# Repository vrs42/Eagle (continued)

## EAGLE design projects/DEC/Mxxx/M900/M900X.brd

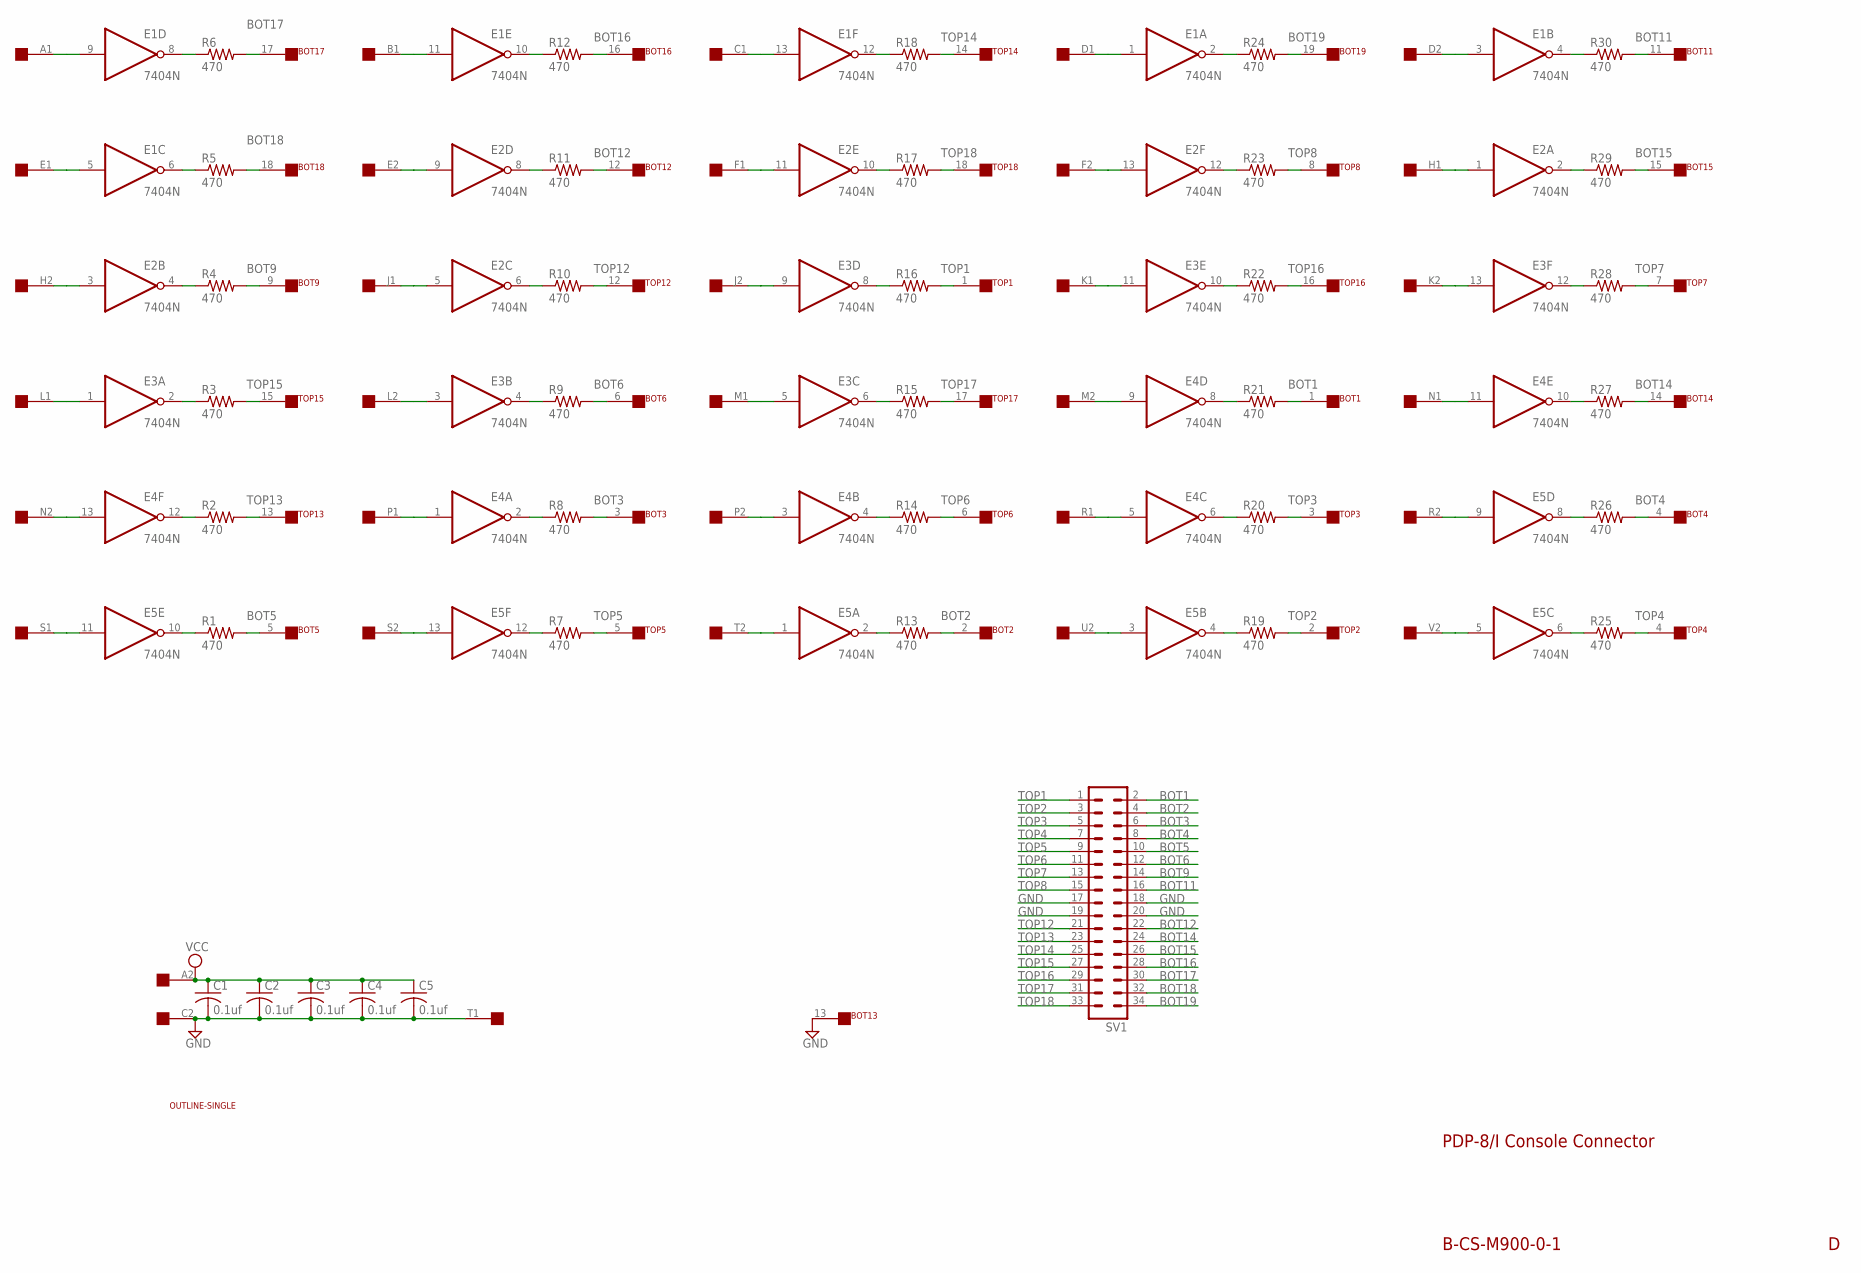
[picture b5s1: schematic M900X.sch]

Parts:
BOT: FLEX19
C1, C2, C3, C4, C5: 0.1uf; C050-025X075
E1, E2, E3, E4, E5: 7404N; DIL14
EDGE: SINGLE; EDGE-CON2
R1, R2, R3, R4, R5, R6, R7, R8, R9, R10, R11, R12, R13, R14, R15, R16, R17, R18, R19, R20, R21, R22, R23, R24, R25, R26, R27, R28, R29, R30: 470; 0207/10
SV1: ML34L
TOP: FLEX19
U$2: OUTLINE-SINGLE; SINGLE

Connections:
BOT1: BOT.1, R21.2, SV1.2
BOT2: BOT.2, R13.2, SV1.4
BOT3: BOT.3, R8.2, SV1.6
BOT4: BOT.4, R26.2, SV1.8
BOT5: BOT.5, R1.2, SV1.10
BOT6: BOT.6, R9.2, SV1.12
BOT9: BOT.9, R4.2, SV1.14
BOT11: BOT.11, R30.2, SV1.16
BOT12: BOT.12, R11.2, SV1.22
BOT14: BOT.14, R27.2, SV1.24
BOT15: BOT.15, R29.2, SV1.26
BOT16: BOT.16, R12.2, SV1.28
BOT17: BOT.17, R6.2, SV1.30
BOT18: BOT.18, R5.2, SV1.32
BOT19: BOT.19, R24.2, SV1.34
GND: BOT.13, C1.2, C2.2, C3.2, C4.2, C5.2, E1.7 (GND), E2.7 (GND), E3.7 (GND), E4.7 (GND), E5.7 (GND), EDGE.C2, EDGE.T1, SV1.17, SV1.18, SV1.19, SV1.20
unnamed: E1.9 (I), EDGE.A1
unnamed: E1.8 (O), R6.1
unnamed: E1.6 (O), R5.1
unnamed: E2.4 (O), R4.1
unnamed: E3.2 (O), R3.1
unnamed: E4.12 (O), R2.1
unnamed: E2.3 (I), EDGE.H2
unnamed: E5.11 (I), EDGE.S1
unnamed: E4.13 (I), EDGE.N2
unnamed: E3.1 (I), EDGE.L1
unnamed: E1.5 (I), EDGE.E1
unnamed: E4.1 (I), EDGE.P1
unnamed: E1.11 (I), EDGE.B1
unnamed: E2.9 (I), EDGE.E2
unnamed: E2.5 (I), EDGE.J1
unnamed: E3.3 (I), EDGE.L2
unnamed: E5.13 (I), EDGE.S2
unnamed: E4.2 (O), R8.1
unnamed: E3.4 (O), R9.1
unnamed: E2.6 (O), R10.1
unnamed: E2.8 (O), R11.1
unnamed: E1.10 (O), R12.1
unnamed: E5.12 (O), R7.1
unnamed: E5.10 (O), R1.1
unnamed: E4.3 (I), EDGE.P2
unnamed: E1.13 (I), EDGE.C1
unnamed: E2.11 (I), EDGE.F1
unnamed: E3.9 (I), EDGE.J2
unnamed: E3.5 (I), EDGE.M1
unnamed: E5.1 (I), EDGE.T2
unnamed: E5.2 (O), R13.1
unnamed: E4.4 (O), R14.1
unnamed: E3.6 (O), R15.1
unnamed: E3.8 (O), R16.1
unnamed: E1.12 (O), R18.1
unnamed: E2.10 (O), R17.1
unnamed: E5.4 (O), R19.1
unnamed: E4.6 (O), R20.1
unnamed: E4.8 (O), R21.1
unnamed: E3.10 (O), R22.1
unnamed: E2.12 (O), R23.1
unnamed: E1.2 (O), R24.1
unnamed: E4.5 (I), EDGE.R1
unnamed: E2.13 (I), EDGE.F2
unnamed: E3.11 (I), EDGE.K1
unnamed: E4.9 (I), EDGE.M2
unnamed: E5.3 (I), EDGE.U2
unnamed: E5.9 (I), EDGE.R2
unnamed: E1.1 (I), EDGE.D1
unnamed: E1.3 (I), EDGE.D2
unnamed: E2.1 (I), EDGE.H1
unnamed: E3.13 (I), EDGE.K2
unnamed: E4.11 (I), EDGE.N1
unnamed: E5.5 (I), EDGE.V2
unnamed: E5.6 (O), R25.1
unnamed: E5.8 (O), R26.1
unnamed: E4.10 (O), R27.1
unnamed: E3.12 (O), R28.1
unnamed: E2.2 (O), R29.1
unnamed: E1.4 (O), R30.1
TOP1: R16.2, SV1.1, TOP.1
TOP2: R19.2, SV1.3, TOP.2
TOP3: R20.2, SV1.5, TOP.3
TOP4: R25.2, SV1.7, TOP.4
TOP5: R7.2, SV1.9, TOP.5
TOP6: R14.2, SV1.11, TOP.6
TOP7: R28.2, SV1.13, TOP.7
TOP8: R23.2, SV1.15, TOP.8
TOP12: R10.2, SV1.21, TOP.12
TOP13: R2.2, SV1.23, TOP.13
TOP14: R18.2, SV1.25, TOP.14
TOP15: R3.2, SV1.27, TOP.15
TOP16: R22.2, SV1.29, TOP.16
TOP17: R15.2, SV1.31, TOP.17
TOP18: R17.2, SV1.33, TOP.18
VCC: C1.1, C2.1, C3.1, C4.1, C5.1, E1.14 (VCC), E2.14 (VCC), E3.14 (VCC), E4.14 (VCC), E5.14 (VCC), EDGE.A2

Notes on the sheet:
B-CS-M900-0-1
PDP-8/I Console Connector

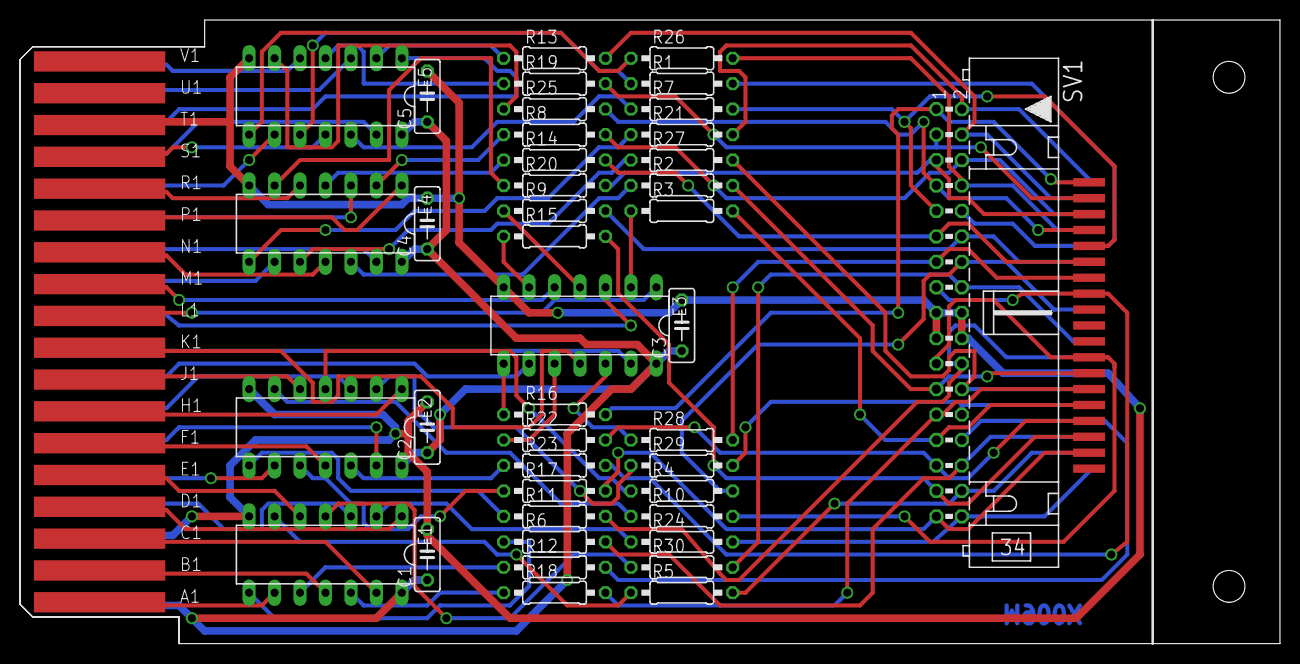
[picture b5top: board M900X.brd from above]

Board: 2 copper layers, 125.7 x 62.2 mm, 45 parts (1 on the bottom side), 92 nets.

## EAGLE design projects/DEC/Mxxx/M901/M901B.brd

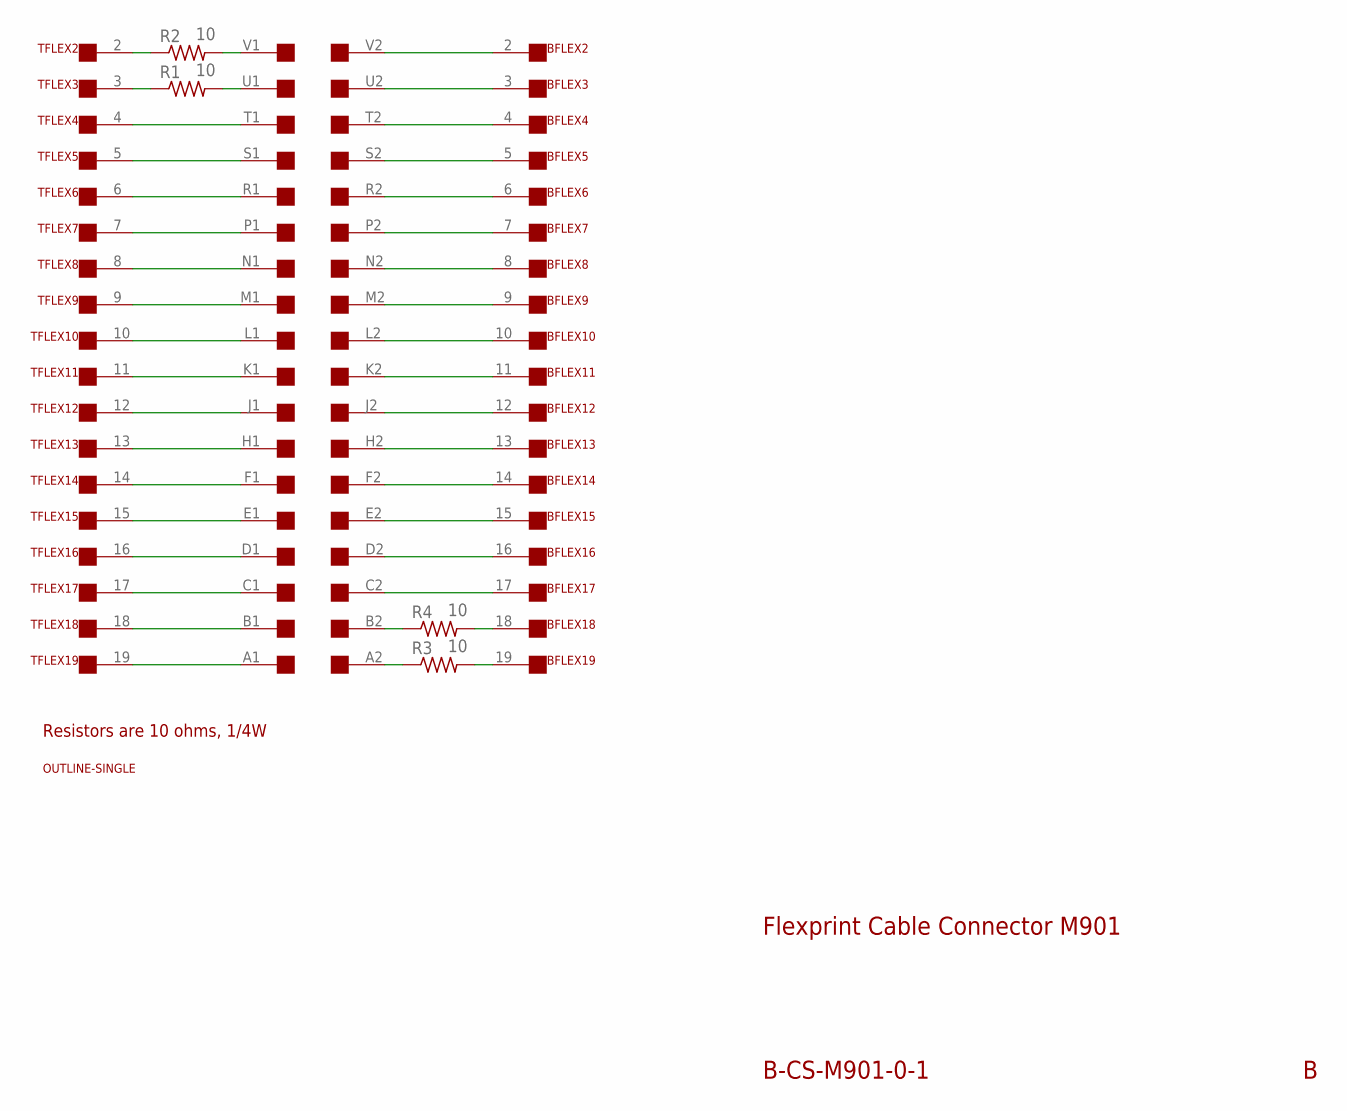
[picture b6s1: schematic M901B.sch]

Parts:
BFLEX: FLEX19
R1, R2, R3, R4: 10; 0207/10
TFLEX: FLEX19
U$1: SINGLE; EDGE-CON2
U$2: OUTLINE-SINGLE; SINGLE

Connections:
unnamed: TFLEX.4, U$1.T1
unnamed: TFLEX.19, U$1.A1
unnamed: TFLEX.17, U$1.C1
unnamed: TFLEX.16, U$1.D1
unnamed: TFLEX.15, U$1.E1
unnamed: TFLEX.14, U$1.F1
unnamed: TFLEX.13, U$1.H1
unnamed: TFLEX.12, U$1.J1
unnamed: TFLEX.11, U$1.K1
unnamed: TFLEX.10, U$1.L1
unnamed: TFLEX.9, U$1.M1
unnamed: TFLEX.8, U$1.N1
unnamed: TFLEX.7, U$1.P1
unnamed: TFLEX.6, U$1.R1
unnamed: TFLEX.5, U$1.S1
unnamed: BFLEX.3, U$1.U2
unnamed: BFLEX.6, U$1.R2
unnamed: BFLEX.8, U$1.N2
unnamed: BFLEX.10, U$1.L2
unnamed: BFLEX.12, U$1.J2
unnamed: BFLEX.14, U$1.F2
unnamed: BFLEX.16, U$1.D2
unnamed: BFLEX.15, U$1.E2
unnamed: BFLEX.17, U$1.C2
unnamed: BFLEX.13, U$1.H2
unnamed: R3.1, U$1.A2
unnamed: BFLEX.11, U$1.K2
unnamed: BFLEX.19, R3.2
unnamed: BFLEX.9, U$1.M2
unnamed: BFLEX.18, R4.2
unnamed: BFLEX.7, U$1.P2
unnamed: R4.1, U$1.B2
unnamed: BFLEX.5, U$1.S2
unnamed: BFLEX.4, U$1.T2
unnamed: R2.1, TFLEX.2
unnamed: BFLEX.2, U$1.V2
unnamed: R1.1, TFLEX.3
unnamed: R1.2, U$1.U1
unnamed: R2.2, U$1.V1
unnamed: TFLEX.18, U$1.B1

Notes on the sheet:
Flexprint Cable Connector M901
B-CS-M901-0-1
Resistors are 10 ohms, 1/4W

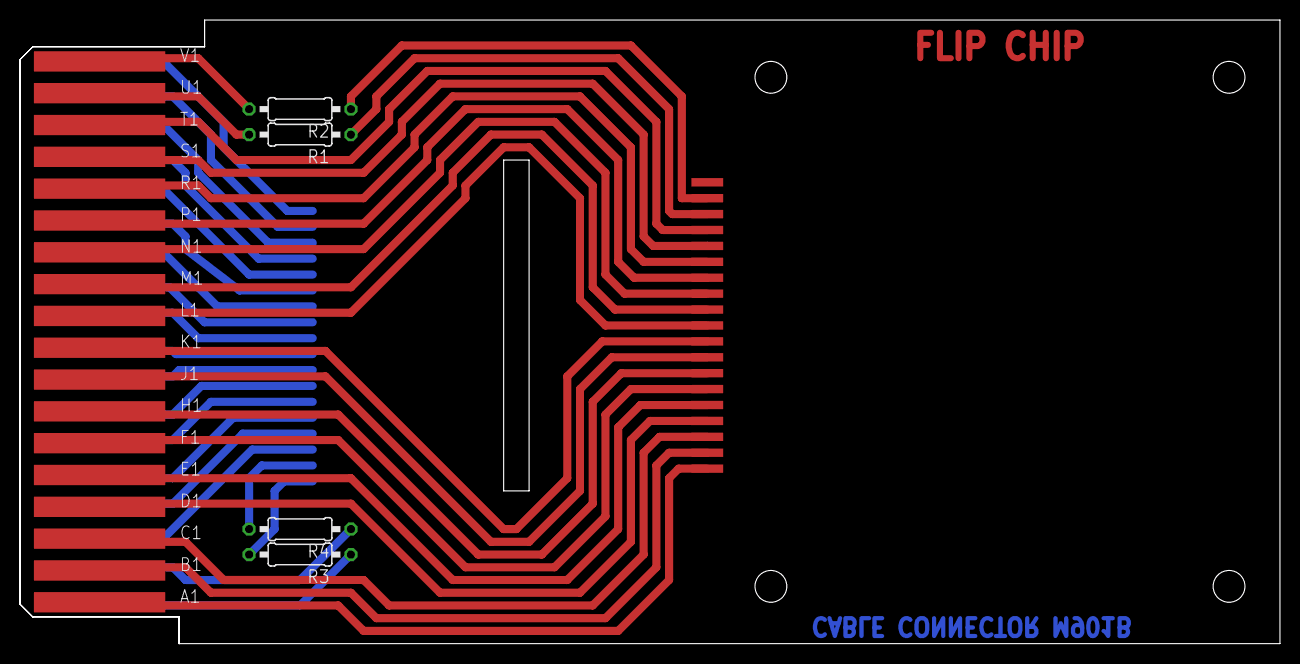
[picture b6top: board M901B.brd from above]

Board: 2 copper layers, 125.7 x 62.2 mm, 9 parts (1 on the bottom side), 40 nets.

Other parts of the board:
U$3: FLIPCHIP

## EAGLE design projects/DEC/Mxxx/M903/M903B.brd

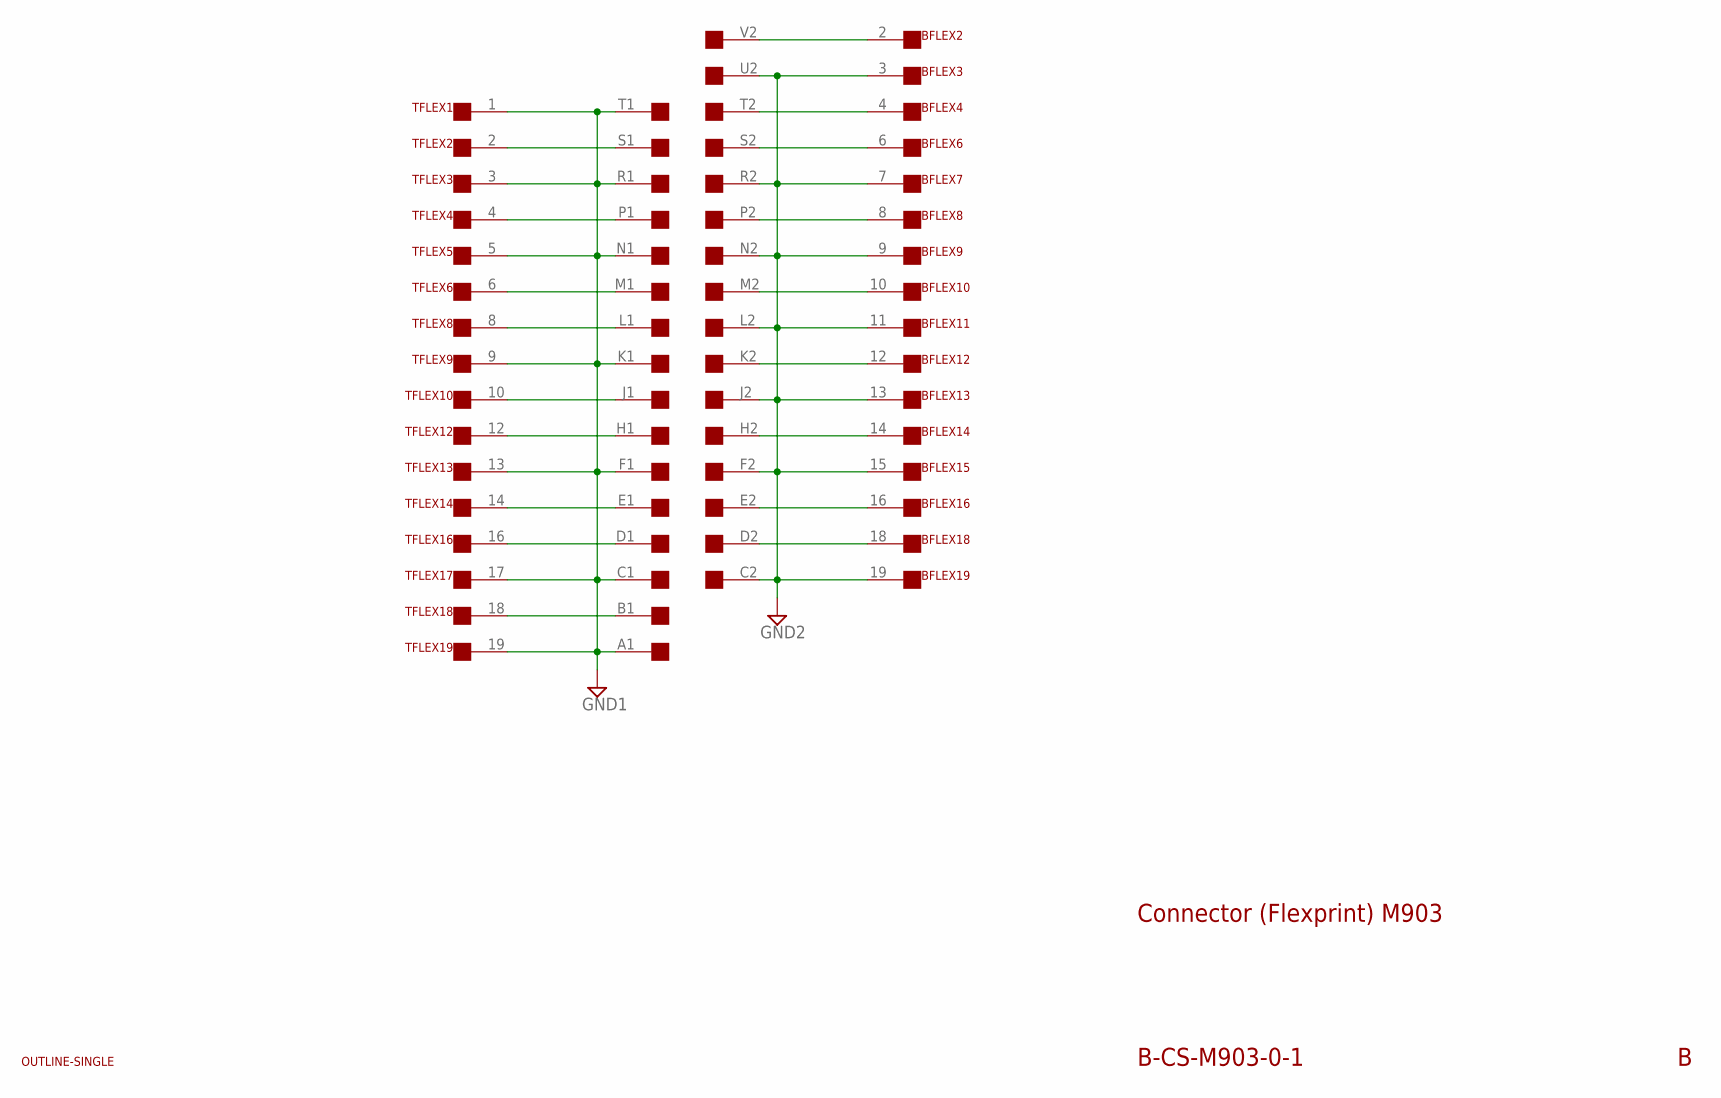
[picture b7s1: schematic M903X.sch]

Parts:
BFLEX: FLEX19
TFLEX: FLEX19
U$1: SINGLE; EDGE-CON2
U$2: OUTLINE-SINGLE; SINGLE

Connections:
GND1: TFLEX.1, TFLEX.3, TFLEX.5, TFLEX.9, TFLEX.13, TFLEX.17, TFLEX.19, U$1.A1, U$1.C1, U$1.F1, U$1.K1, U$1.N1, U$1.R1, U$1.T1
GND2: BFLEX.3, BFLEX.7, BFLEX.9, BFLEX.11, BFLEX.13, BFLEX.15, BFLEX.19, U$1.C2, U$1.F2, U$1.J2, U$1.L2, U$1.N2, U$1.R2, U$1.U2
unnamed: TFLEX.16, U$1.D1
unnamed: TFLEX.14, U$1.E1
unnamed: TFLEX.12, U$1.H1
unnamed: TFLEX.10, U$1.J1
unnamed: TFLEX.8, U$1.L1
unnamed: TFLEX.6, U$1.M1
unnamed: TFLEX.4, U$1.P1
unnamed: TFLEX.2, U$1.S1
unnamed: BFLEX.18, U$1.D2
unnamed: BFLEX.16, U$1.E2
unnamed: BFLEX.14, U$1.H2
unnamed: BFLEX.12, U$1.K2
unnamed: BFLEX.10, U$1.M2
unnamed: BFLEX.8, U$1.P2
unnamed: BFLEX.6, U$1.S2
unnamed: BFLEX.4, U$1.T2
unnamed: BFLEX.2, U$1.V2
unnamed: TFLEX.18, U$1.B1

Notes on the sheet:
Connector (Flexprint) M903
B-CS-M903-0-1

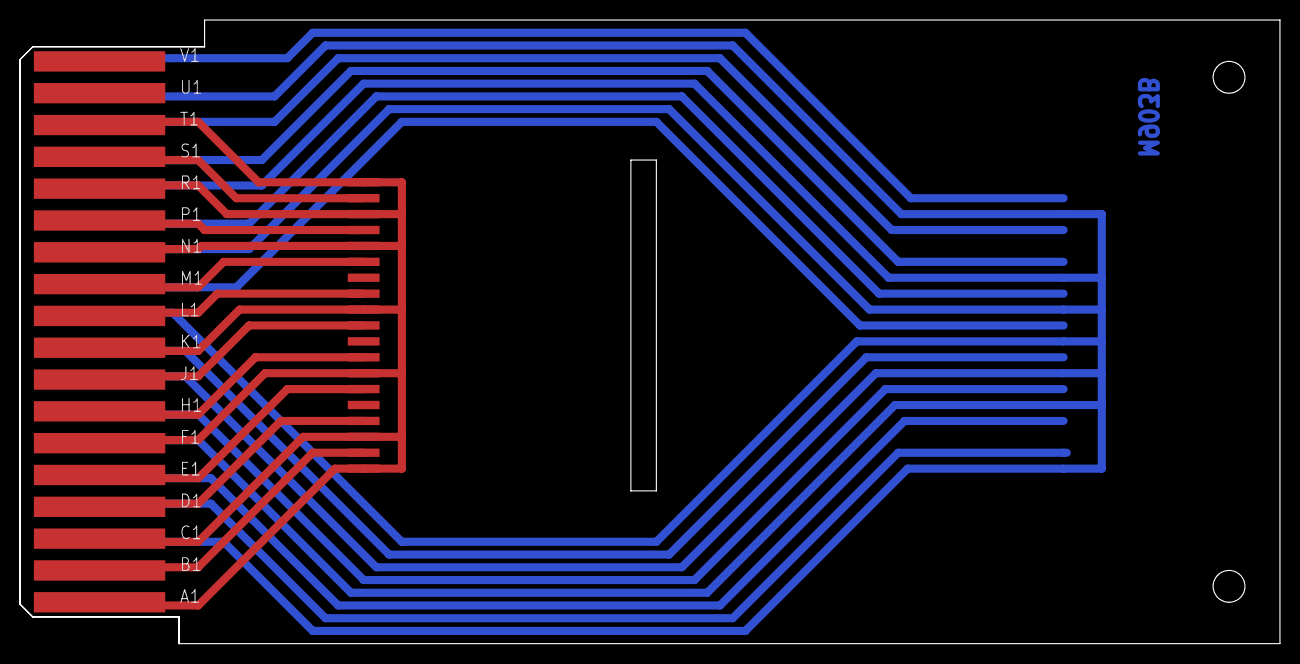
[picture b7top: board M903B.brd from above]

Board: 2 copper layers, 125.7 x 62.2 mm, 4 parts (1 on the bottom side), 20 nets.
